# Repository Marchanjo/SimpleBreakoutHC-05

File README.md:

Simple Breakout Board for HC-05 serial Bluetooth
========================

O módulo Bluetooth HC-05 é barato e fácil de usar, existem vários sites com instruções. Quando se tem somente o módulo é interessante uma breakout boad para facilitar a conexão. 

Este projeto contempla os arquivos necessários para fazer esta breakout board bem como o código para testá-la.

Mais informações no meu Blog: [http://marchanjo.blogspot.com.br/2015/07/breakout-board-para-modulo-hc-05.html](http://marchanjo.blogspot.com.br/2015/07/breakout-board-para-modulo-hc-05.html)

*Esquemático:*

*PCB:*

*Placa montada:*

Mapa do projeto
---------------
* **/Firmware** - Código Arduino
* **/Hardware** - Arquivos de design Eagle esquemático, PCB, figuras e Gerbers.

Licença
-------
O hardware e o software estão disponiveis em [Creative Commons Attribution-ShareAlike 4.0 International License.](http://creativecommons.org/licenses/by-sa/4.0/)

The hardware and the software are released under [Creative Commons Attribution-ShareAlike 4.0 International License.](http://creativecommons.org/licenses/by-sa/4.0/)

Distribuido como está, nenhuma garantia é dada.

Distributed as-is; no warranty is given.

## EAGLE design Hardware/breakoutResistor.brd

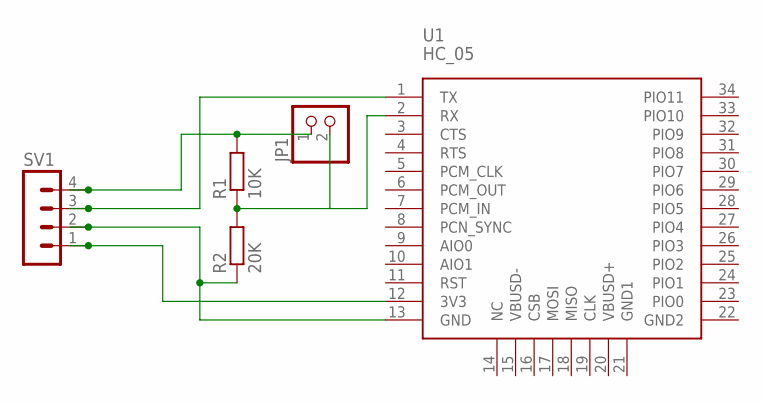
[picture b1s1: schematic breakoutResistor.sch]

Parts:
JP1: PINHD-1X2; 1X02
R1: 10K; R0805
R2: 20K; R0805
SV1: MA04-1
U1: HC_05; BLUETOOTH_SMD

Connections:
unnamed: R2.1, SV1.2, U1.13 (GND)
unnamed: JP1.1, R1.2, SV1.4
unnamed: SV1.3, U1.1 (TX)
unnamed: SV1.1, U1.12 (3V3)
unnamed: JP1.2, R1.1, R2.2, U1.2 (RX)

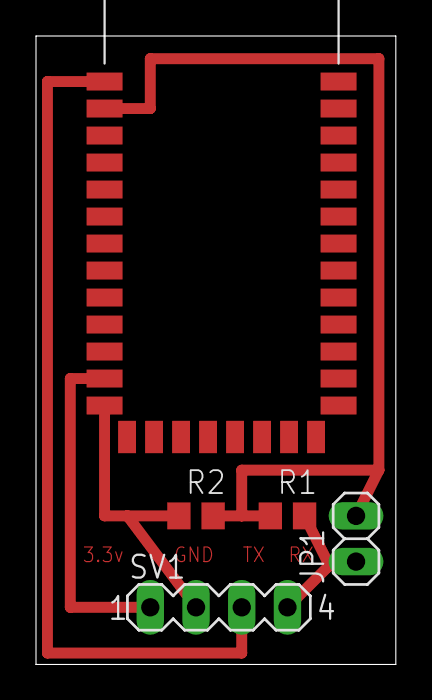
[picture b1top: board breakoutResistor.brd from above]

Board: 2 copper layers, 20.0 x 34.9 mm, 5 parts (0 on the bottom side), 5 nets.

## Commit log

2015-07-20 Primeira carga
2015-07-20 Imagem final
2015-07-20 Atualização do Código
2015-07-20 Atualizações
2015-07-20 Atualização
